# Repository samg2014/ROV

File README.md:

##*About This Project*
This respository is for all files related to modifications of the [Sea Perch](www.seaperch.org) ROV. The overall goals of this project are to:
* Make the vehicle controllable from a microcontroller or computer.
* Enable the vehicle to have the potential to be self contained. This includes:
  * Making the controller waterproof so it can be deployed on the vehicle,
  * Making the battery waterproof so it can go on the vehicle,
  * Writing autonomy scripts for the vehicle.
* Make the vehicle 'smart', including:
  * Autonomy, regardless of controller location (land or vehicle)
  * Sensor integration (IMUs...)
* Anything else we think of as we go.

##*Organization*
###Software Directory
The Software directory houses all of the code, Arduino or otherwise, associated with this project. It have two main subdirectories: Vehicle and Computer.
####Vehicle
The Vehicle subdirectory is for all sketches that are to be uploaded to the vehicle controller Arduino.
####Computer
The Computer subdirectory is for all support software that may exist. This could potentially be remote interfaces, wireless command sequence uploaders, command generators and much more.
###Electrical Directory
The Electrical directory is for schematics eagle design files and related to designing the vehicle controller. Additionally it should include parts lists and assembly processes if applicable.
###Hardware Directory
The Hardware Design directory is for potential CAD design files for the main structure of the vehicle.

##*Resources*
* [Google Drive folder](https://drive.google.com/folderview?id=0B45sdQ03G0k-UUpMSS1selFKa1k&usp=sharing) 
* [Sea Perch](www.seaperch.org) 
* [Sea Perch BOM](http://www.seaperch.org/Parts_List) (Note: requires free account) 
* [Sparkfun](www.sparkfun.com) (Parts)

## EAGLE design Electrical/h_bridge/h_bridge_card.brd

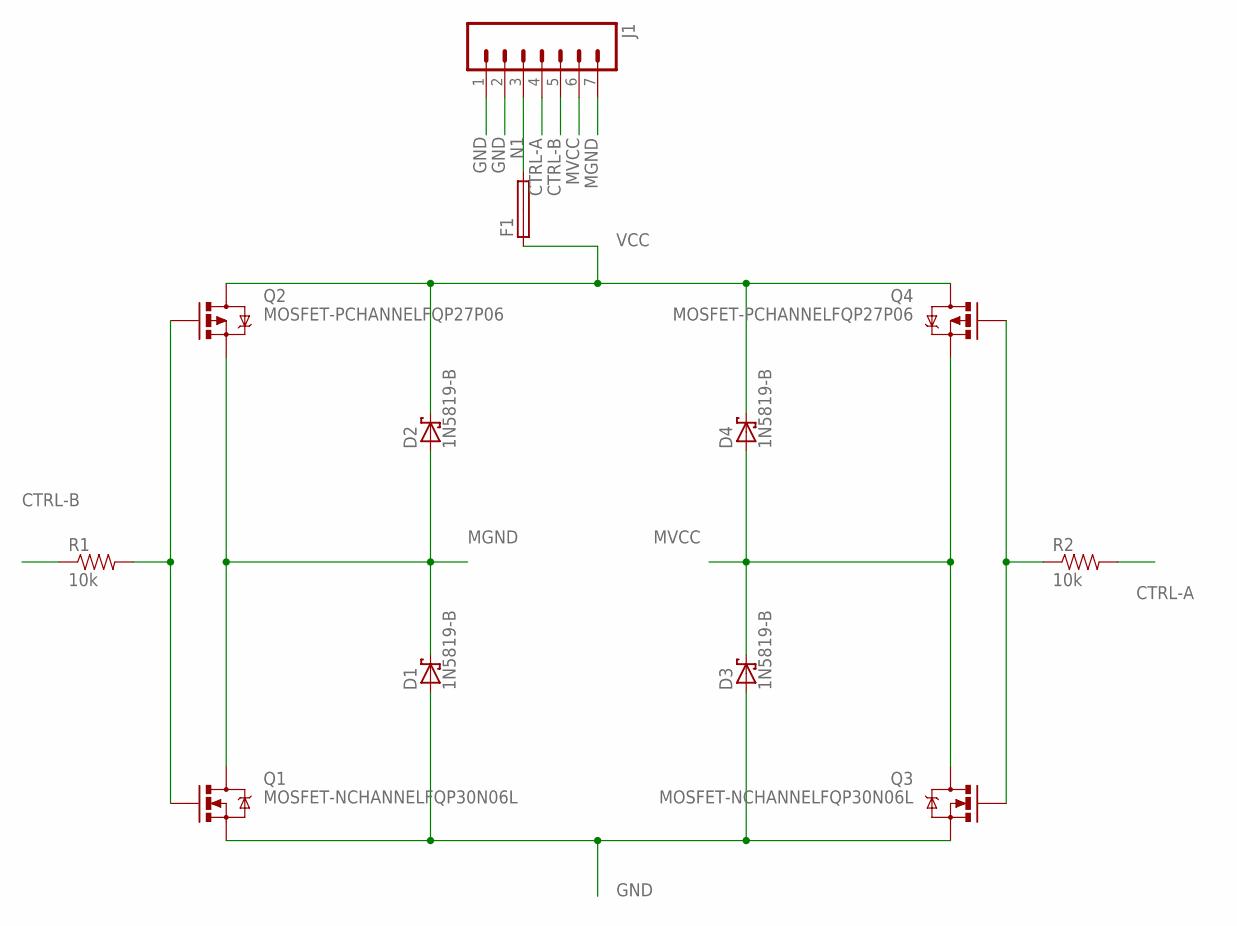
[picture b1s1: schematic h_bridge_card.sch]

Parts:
D1, D2, D3, D4: 1N5819-B; DO41-7.6
F1: SHK20L
J1: M07LOCK; 1X07_LOCK
Q1, Q3: MOSFET-NCHANNELFQP30N06L; TO220V
Q2, Q4: MOSFET-PCHANNELFQP27P06; TO220V
R1, R2: 10k; AXIAL-0.3

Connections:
CTRL-A: J1.4, R2.P$2 (2)
CTRL-B: J1.5, R1.P$1 (1)
GND: D1.A, D3.A, J1.1, J1.2, Q1.3 (S), Q3.3 (S)
MGND: D1.C, D2.A, J1.7, Q1.2 (D), Q2.3 (S)
MVCC: D3.C, D4.A, J1.6, Q3.2 (D), Q4.3 (S)
N1: F1.2A, J1.3
unnamed: Q3.1 (G), Q4.1 (G), R2.P$1 (1)
unnamed: Q1.1 (G), Q2.1 (G), R1.P$2 (2)
VCC: D2.C, D4.C, F1.1A, Q2.2 (D), Q4.2 (D)

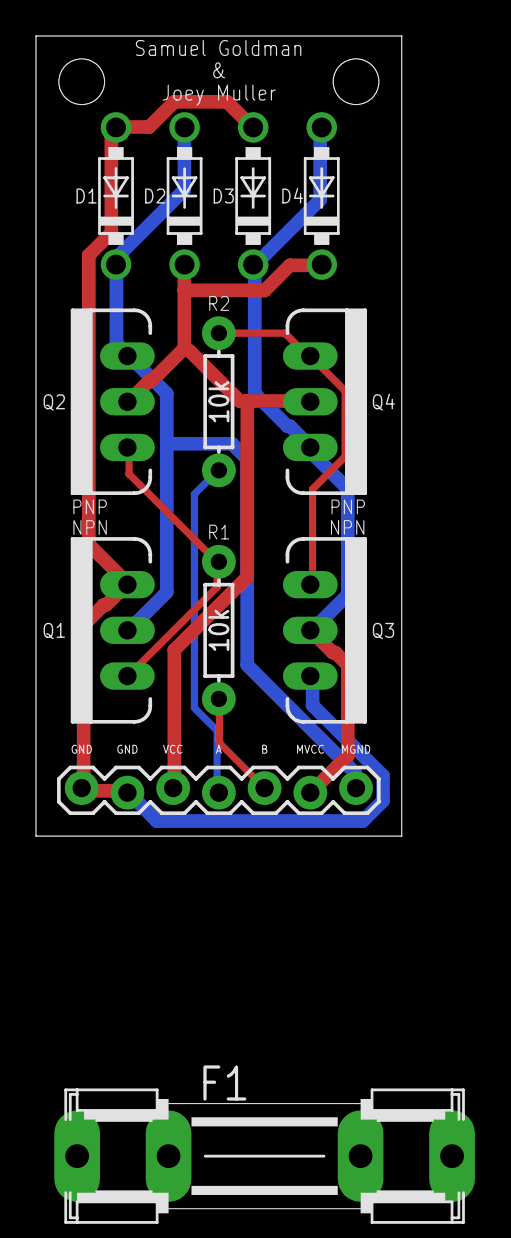
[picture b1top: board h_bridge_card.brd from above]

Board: 2 copper layers, 20.3 x 44.5 mm, 12 parts (0 on the bottom side), 9 nets.

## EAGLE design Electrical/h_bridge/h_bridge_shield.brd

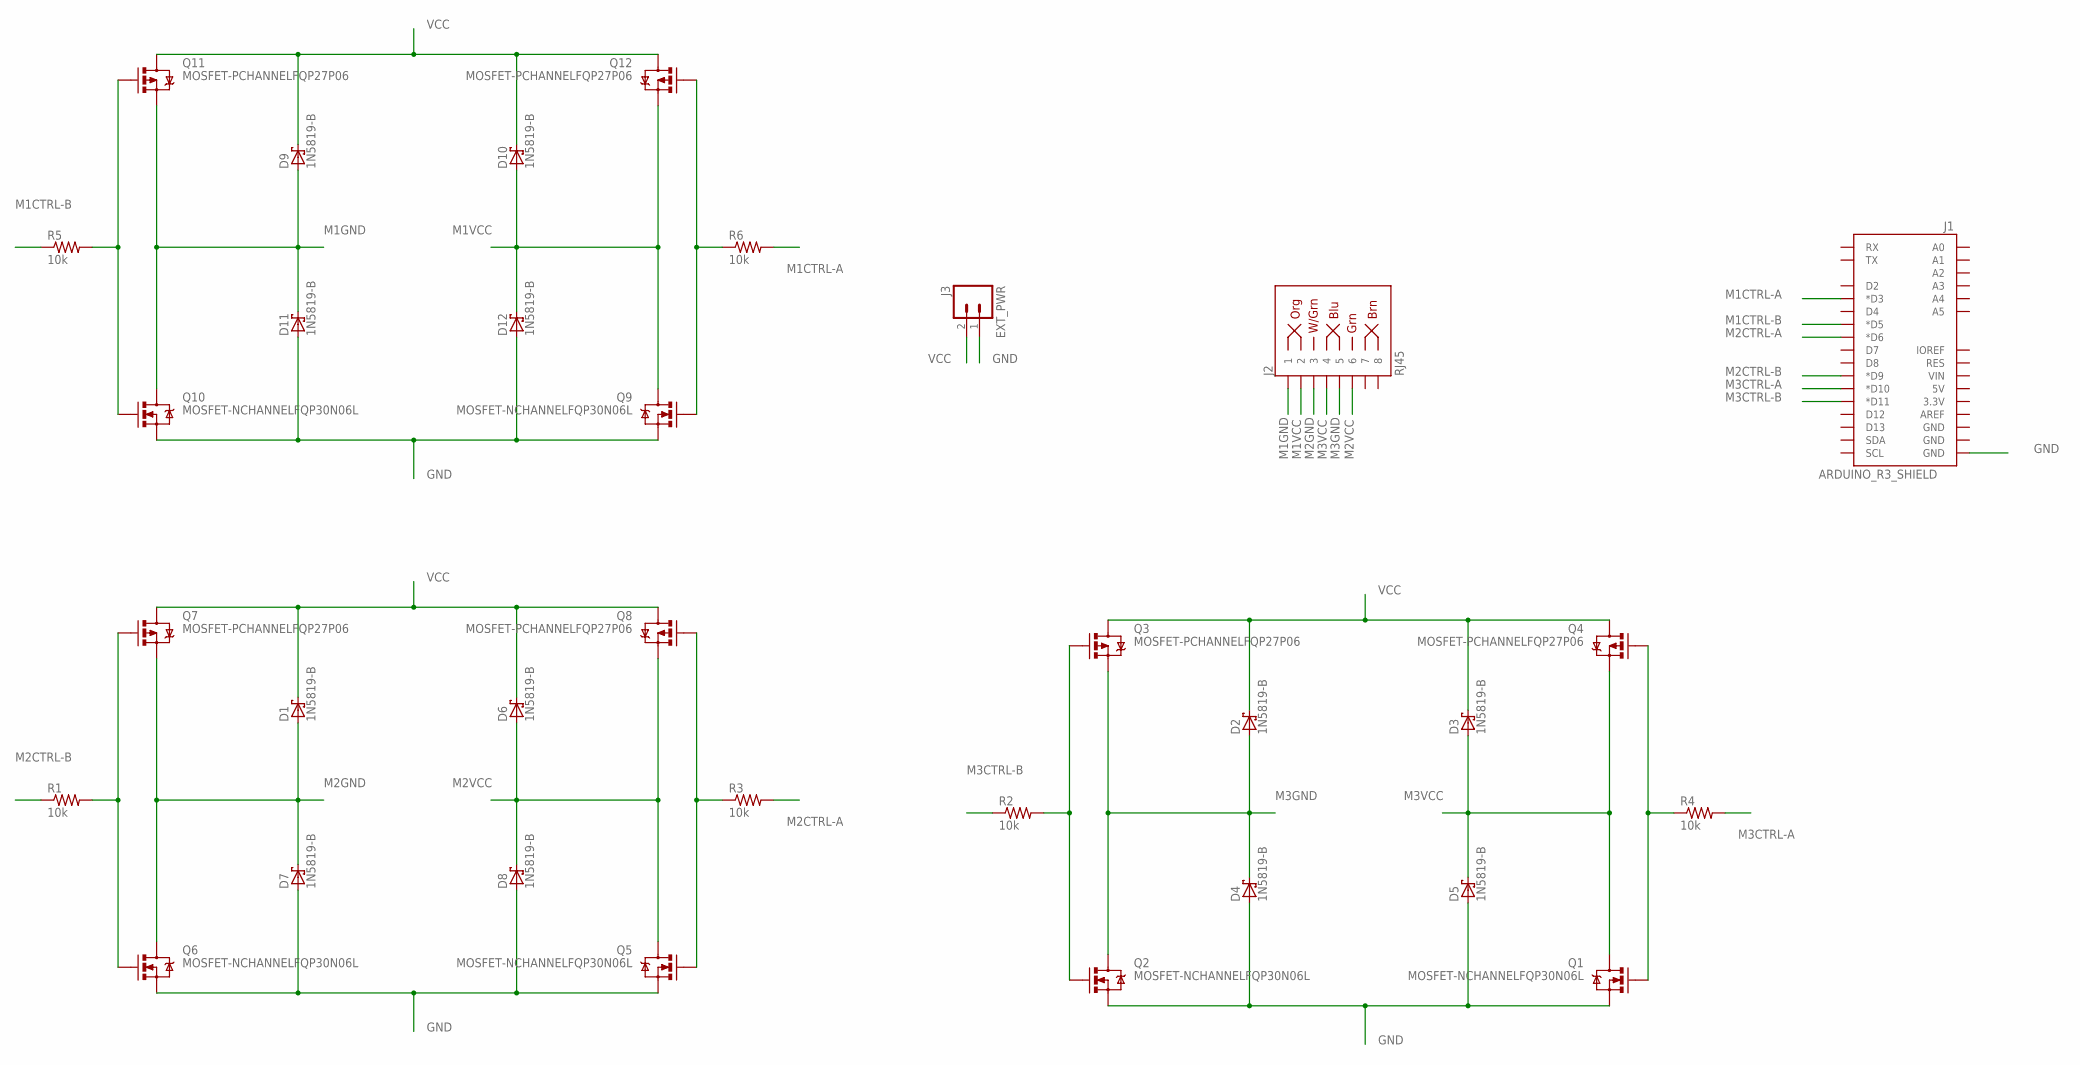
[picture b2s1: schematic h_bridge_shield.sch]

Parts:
D1, D2, D3, D4, D5, D6, D7, D8, D9, D10, D11, D12: 1N5819-B; DO41-7.6
J1: ARDUINO_R3_SHIELD; UNO_R3_SHIELD
J2: RJ45; RJ45-8
J3: EXT_PWR; JST-2-PTH-VERT
Q1, Q2, Q5, Q6, Q9, Q10: MOSFET-NCHANNELFQP30N06L; TO220V
Q3, Q4, Q7, Q8, Q11, Q12: MOSFET-PCHANNELFQP27P06; TO220V
R1, R2, R3, R4, R5, R6: 10k; AXIAL-0.3

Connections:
GND: D4.A, D5.A, D7.A, D8.A, D11.A, D12.A, J1.GND@0 (GND), J3.1, Q1.3 (S), Q2.3 (S), Q5.3 (S), Q6.3 (S), Q9.3 (S), Q10.3 (S)
M1CTRL-A: J1.D3 (*D3), R6.P$2 (2)
M1CTRL-B: J1.D5 (*D5), R5.P$1 (1)
M1GND: D9.A, D11.C, J2.1, Q10.2 (D), Q11.3 (S)
M1VCC: D10.A, D12.C, J2.2, Q9.2 (D), Q12.3 (S)
M2CTRL-A: J1.D6 (*D6), R3.P$2 (2)
M2CTRL-B: J1.D9 (*D9), R1.P$1 (1)
M2GND: D1.A, D7.C, J2.3, Q6.2 (D), Q7.3 (S)
M2VCC: D6.A, D8.C, J2.6, Q5.2 (D), Q8.3 (S)
M3CTRL-A: J1.D10 (*D10), R4.P$2 (2)
M3CTRL-B: J1.D11 (*D11), R2.P$1 (1)
M3GND: D2.A, D4.C, J2.5, Q2.2 (D), Q3.3 (S)
M3VCC: D3.A, D5.C, J2.4, Q1.2 (D), Q4.3 (S)
unnamed: Q5.1 (G), Q8.1 (G), R3.P$1 (1)
unnamed: Q6.1 (G), Q7.1 (G), R1.P$2 (2)
unnamed: Q9.1 (G), Q12.1 (G), R6.P$1 (1)
unnamed: Q10.1 (G), Q11.1 (G), R5.P$2 (2)
unnamed: Q1.1 (G), Q4.1 (G), R4.P$1 (1)
unnamed: Q2.1 (G), Q3.1 (G), R2.P$2 (2)
VCC: D1.C, D2.C, D3.C, D6.C, D9.C, D10.C, J3.2, Q3.2 (D), Q4.2 (D), Q7.2 (D), Q8.2 (D), Q11.2 (D), Q12.2 (D)

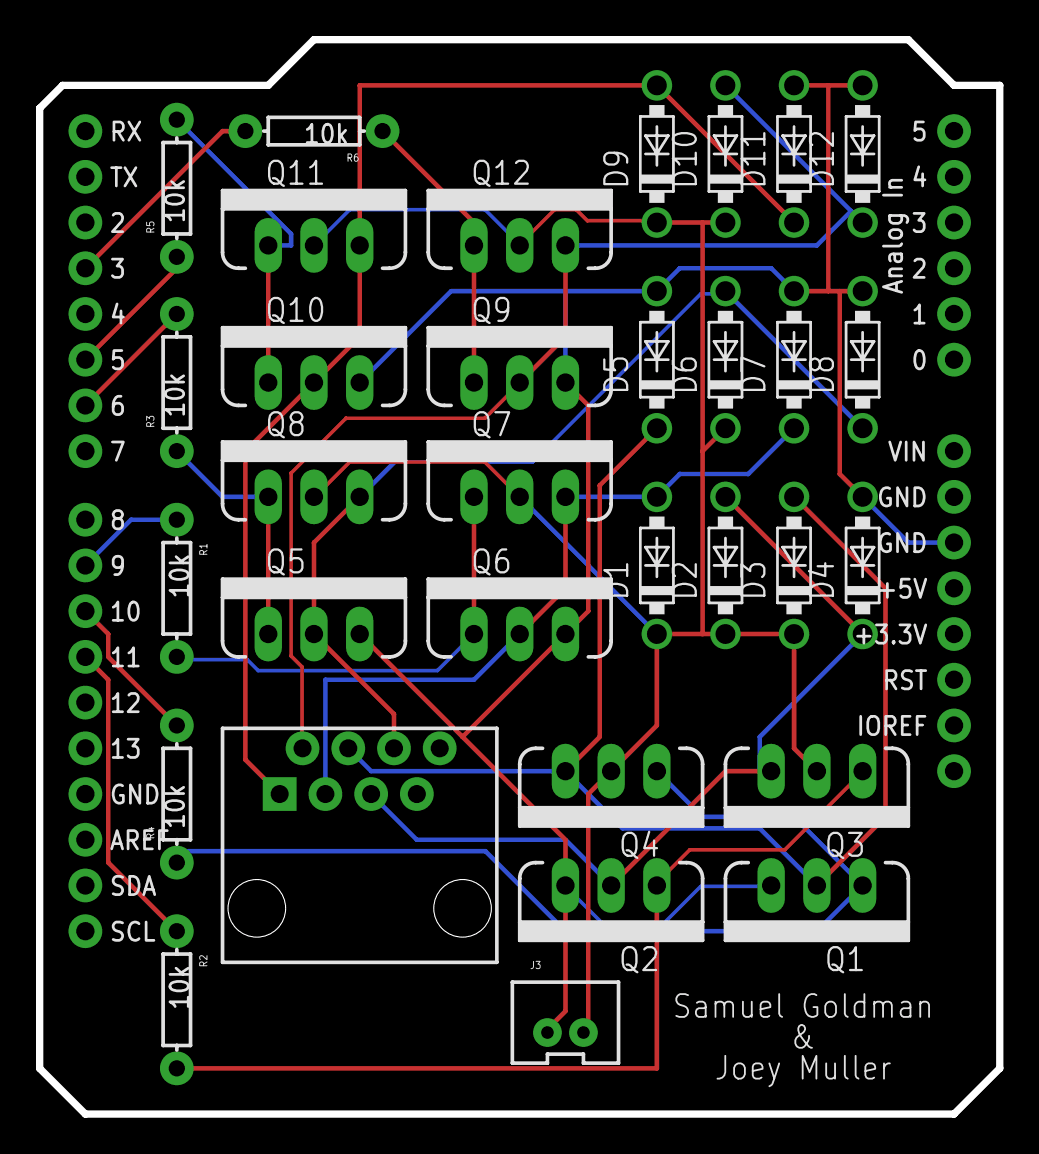
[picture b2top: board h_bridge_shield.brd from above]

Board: 2 copper layers, 53.3 x 59.7 mm, 33 parts (0 on the bottom side), 20 nets.

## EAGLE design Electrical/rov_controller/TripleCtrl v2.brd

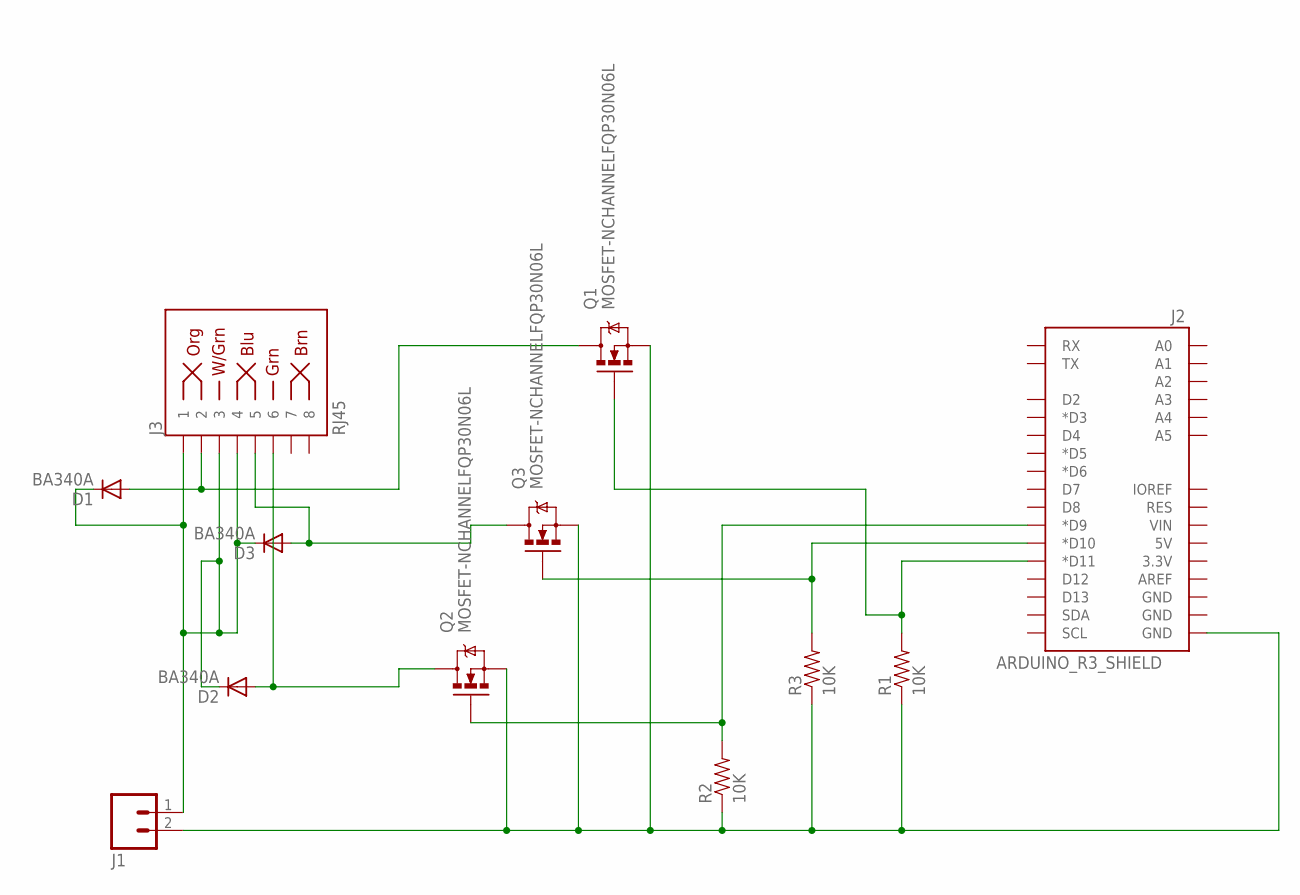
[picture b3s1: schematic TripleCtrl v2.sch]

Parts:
D1, D2, D3: BA340A; DO41-10
J1: M025MM; SCREWTERMINAL-5MM-2
J2: ARDUINO_R3_SHIELD; UNO_R3_SHIELD
J3: RJ45; RJ45-8
Q1, Q2, Q3: MOSFET-NCHANNELFQP30N06L; TO220V
R1, R2, R3: 10K; AXIAL-0.3-KIT

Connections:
unnamed: D1.C, D2.C, D3.C, J1.1, J3.1, J3.3, J3.4
unnamed: J1.2, J2.GND@0 (GND), Q1.3 (S), Q2.3 (S), Q3.3 (S), R1.P$1 (1), R2.P$1 (1), R3.P$1 (1)
unnamed: D1.A, J3.2, Q1.2 (D)
unnamed: J2.D11 (*D11), Q1.1 (G), R1.P$2 (2)
unnamed: D2.A, J3.6, Q2.2 (D)
unnamed: D3.A, J3.5, Q3.2 (D)
unnamed: J2.D10 (*D10), Q3.1 (G), R3.P$2 (2)
unnamed: J2.D9 (*D9), Q2.1 (G), R2.P$2 (2)

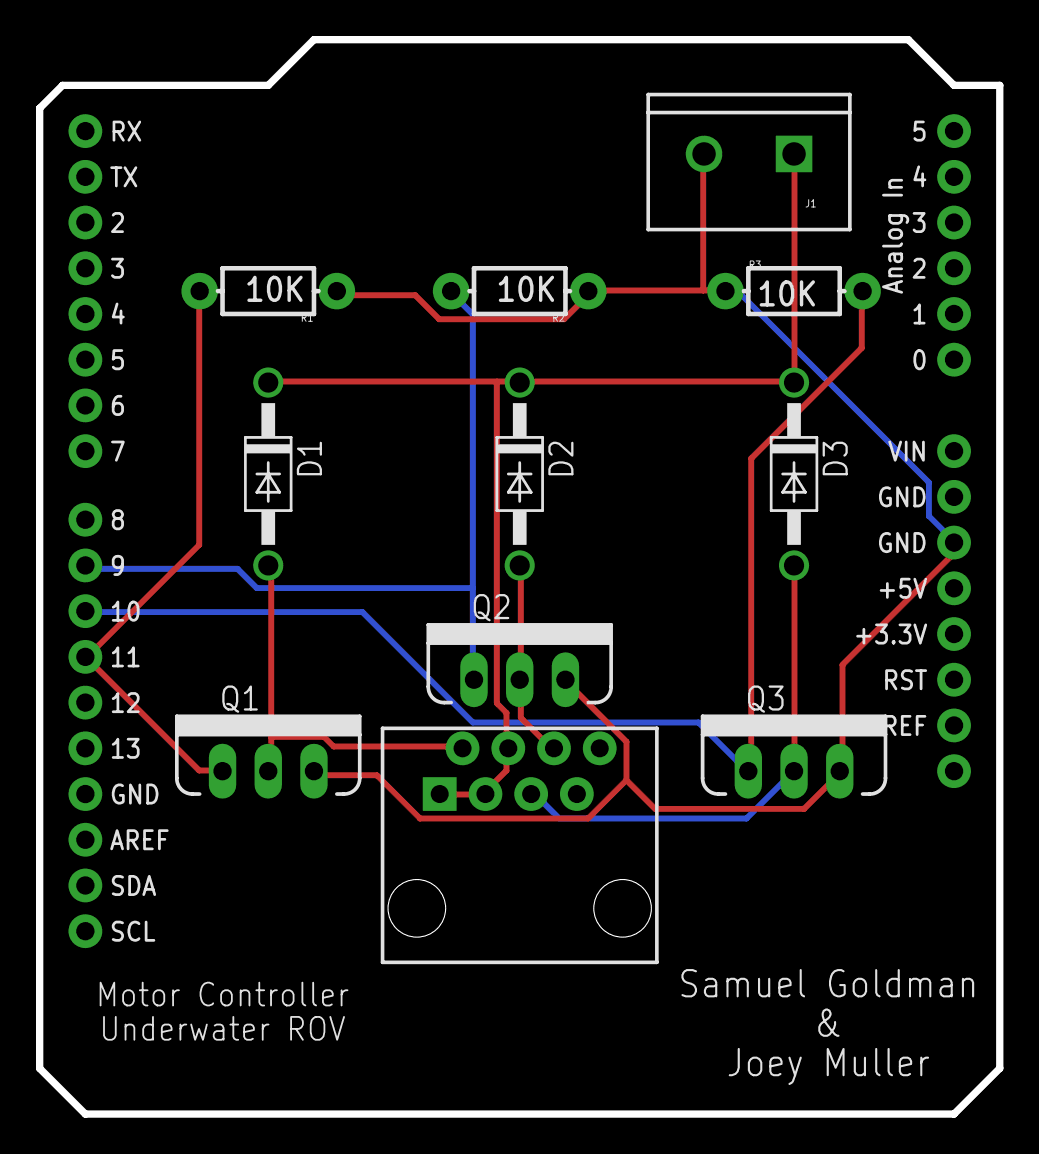
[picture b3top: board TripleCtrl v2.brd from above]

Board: 2 copper layers, 53.3 x 59.7 mm, 12 parts (0 on the bottom side), 8 nets.

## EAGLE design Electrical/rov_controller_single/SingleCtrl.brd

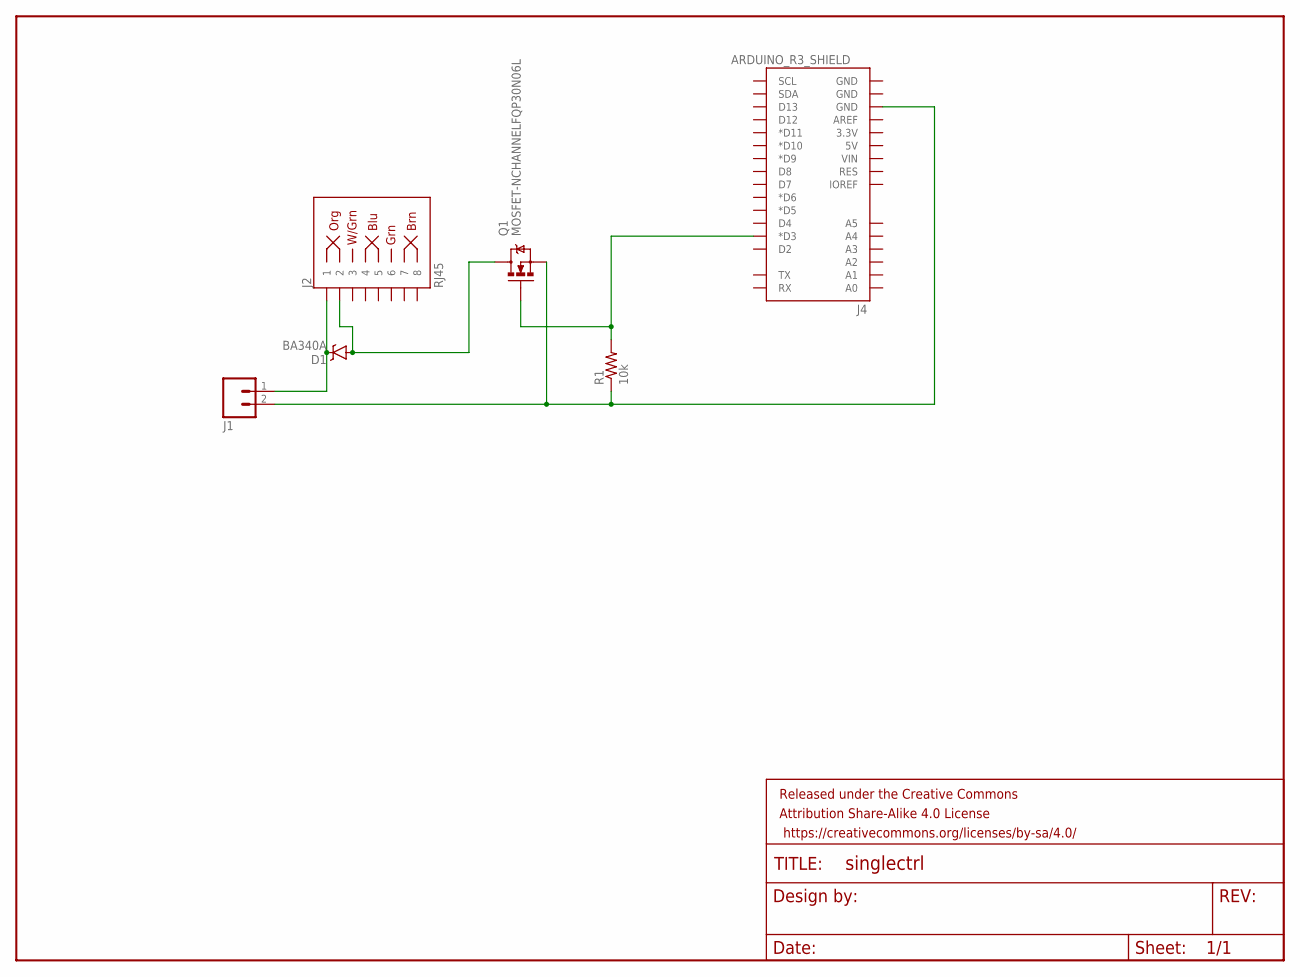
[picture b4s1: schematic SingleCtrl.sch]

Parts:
D1: BA340A; SMA-DIODE
FRAME1: FRAME-LETTER; CREATIVE_COMMONS
J1: M02JST-PTH-2; JST-2-PTH
J2: RJ45; RJ45-8
J4: ARDUINO_R3_SHIELD; UNO_R3_SHIELD
Q1: MOSFET-NCHANNELFQP30N06L; TO220V
R1: 10k; AXIAL-0.3

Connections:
unnamed: D1.C, J1.1, J2.1
unnamed: D1.A, J2.2, Q1.2 (D)
unnamed: J1.2, J4.GND@2 (GND), Q1.3 (S), R1.P$1 (1)
unnamed: J4.D3 (*D3), Q1.1 (G), R1.P$2 (2)

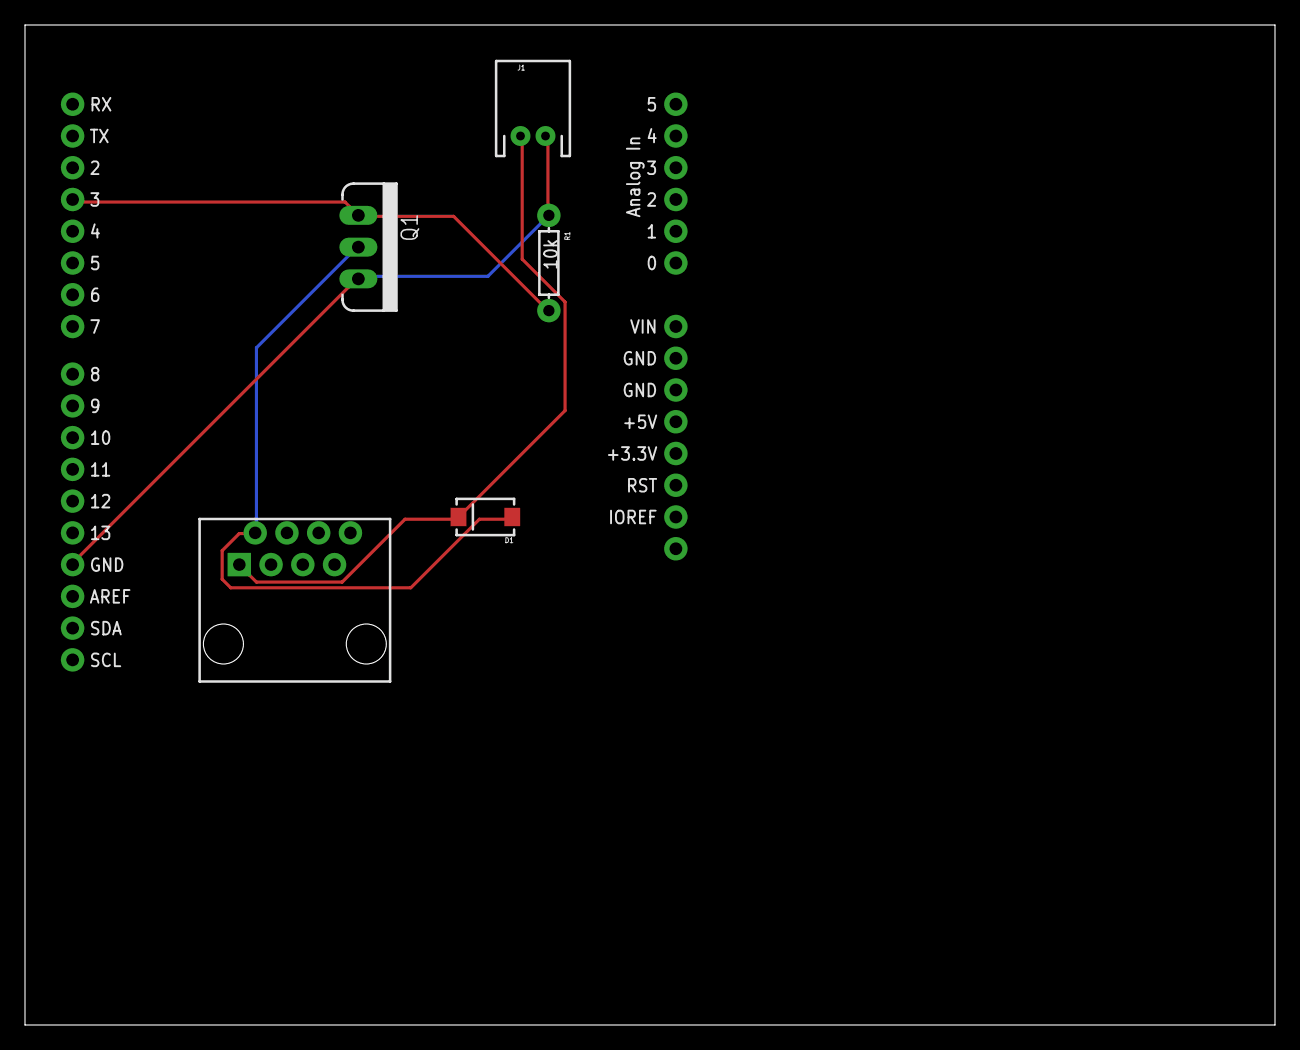
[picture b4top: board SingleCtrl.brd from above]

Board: 2 copper layers, 100.0 x 80.0 mm, 7 parts (0 on the bottom side), 4 nets.

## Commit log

2016-08-07 Create Initial Readme
2016-08-07 Adding three arduino files for testing the bot.
2021-06-14 Add old changes

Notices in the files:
parts and their libraries:
SparkFun-DiscreteSemi: Licensing: Creative Commons ShareAlike 4.0 International - https://creativecommons.org/licenses/by-sa/4.0
SparkFun-Aesthetics: Released under the Creative Commons Attribution Share-Alike 4.0 License
SparkFun-Aesthetics: https://creativecommons.org/licenses/by-sa/4.0
